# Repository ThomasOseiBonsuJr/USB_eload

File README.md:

# USB_eload
This is built off of my previous Electronic Load project, a now deleted repository. I wasn't happy with the state and the direction the project was heading so I am creating a new project.

# Features 
- Constant resistance, constant power, constant current, and constant voltage modes. 
- Software fan control instead of hardware fan control. (Hardware fan control was an interesting idea however I think implementing software fan control will allow for a 'clearer' path for project completion)
- 3D printed enclosure with venting for fan
- OLED display for fan speed, load current, voltage, resistance, power, and temperature

- 20V Max Voltage, 5A max current
- software (maybe hardware if it is more reliable) safety features to prevent overcurrent, overvoltage, and over temperature

- The e load will only be controlled with a usb connection 2.0 to a computer 
- Program that sends commands to change eload parameters (either a terminal program or a exe or something that involves an actual UI, currently leaning  towards a program with a UI due the coding experience that could be gained from that)

# Roadmap
- Rough sketch of enclosure UI
- Research electronic load arcitecture (I think the main reason why I consider the first attempt at this project a failure is because of the minimal amount of research and low expectations of the electronic load. While this project will not come near an off the shelf solution it should at least be suitable for an electronics beginner like me)
- Research constant power, constant resistance, and constant voltage modes
- Learn fusion 360 
- Research the usb 2.0 protocol
- Decide MCU (mcu on old electronic load might be good enough)
- Block diagrams of subsystems in the electronic load
- 1st draft of schematic and layout 
- Review, iterate if needed
- Design enclosure
- Order parts, solder, and test (currently away from home so this last step might be delayed for a bit)

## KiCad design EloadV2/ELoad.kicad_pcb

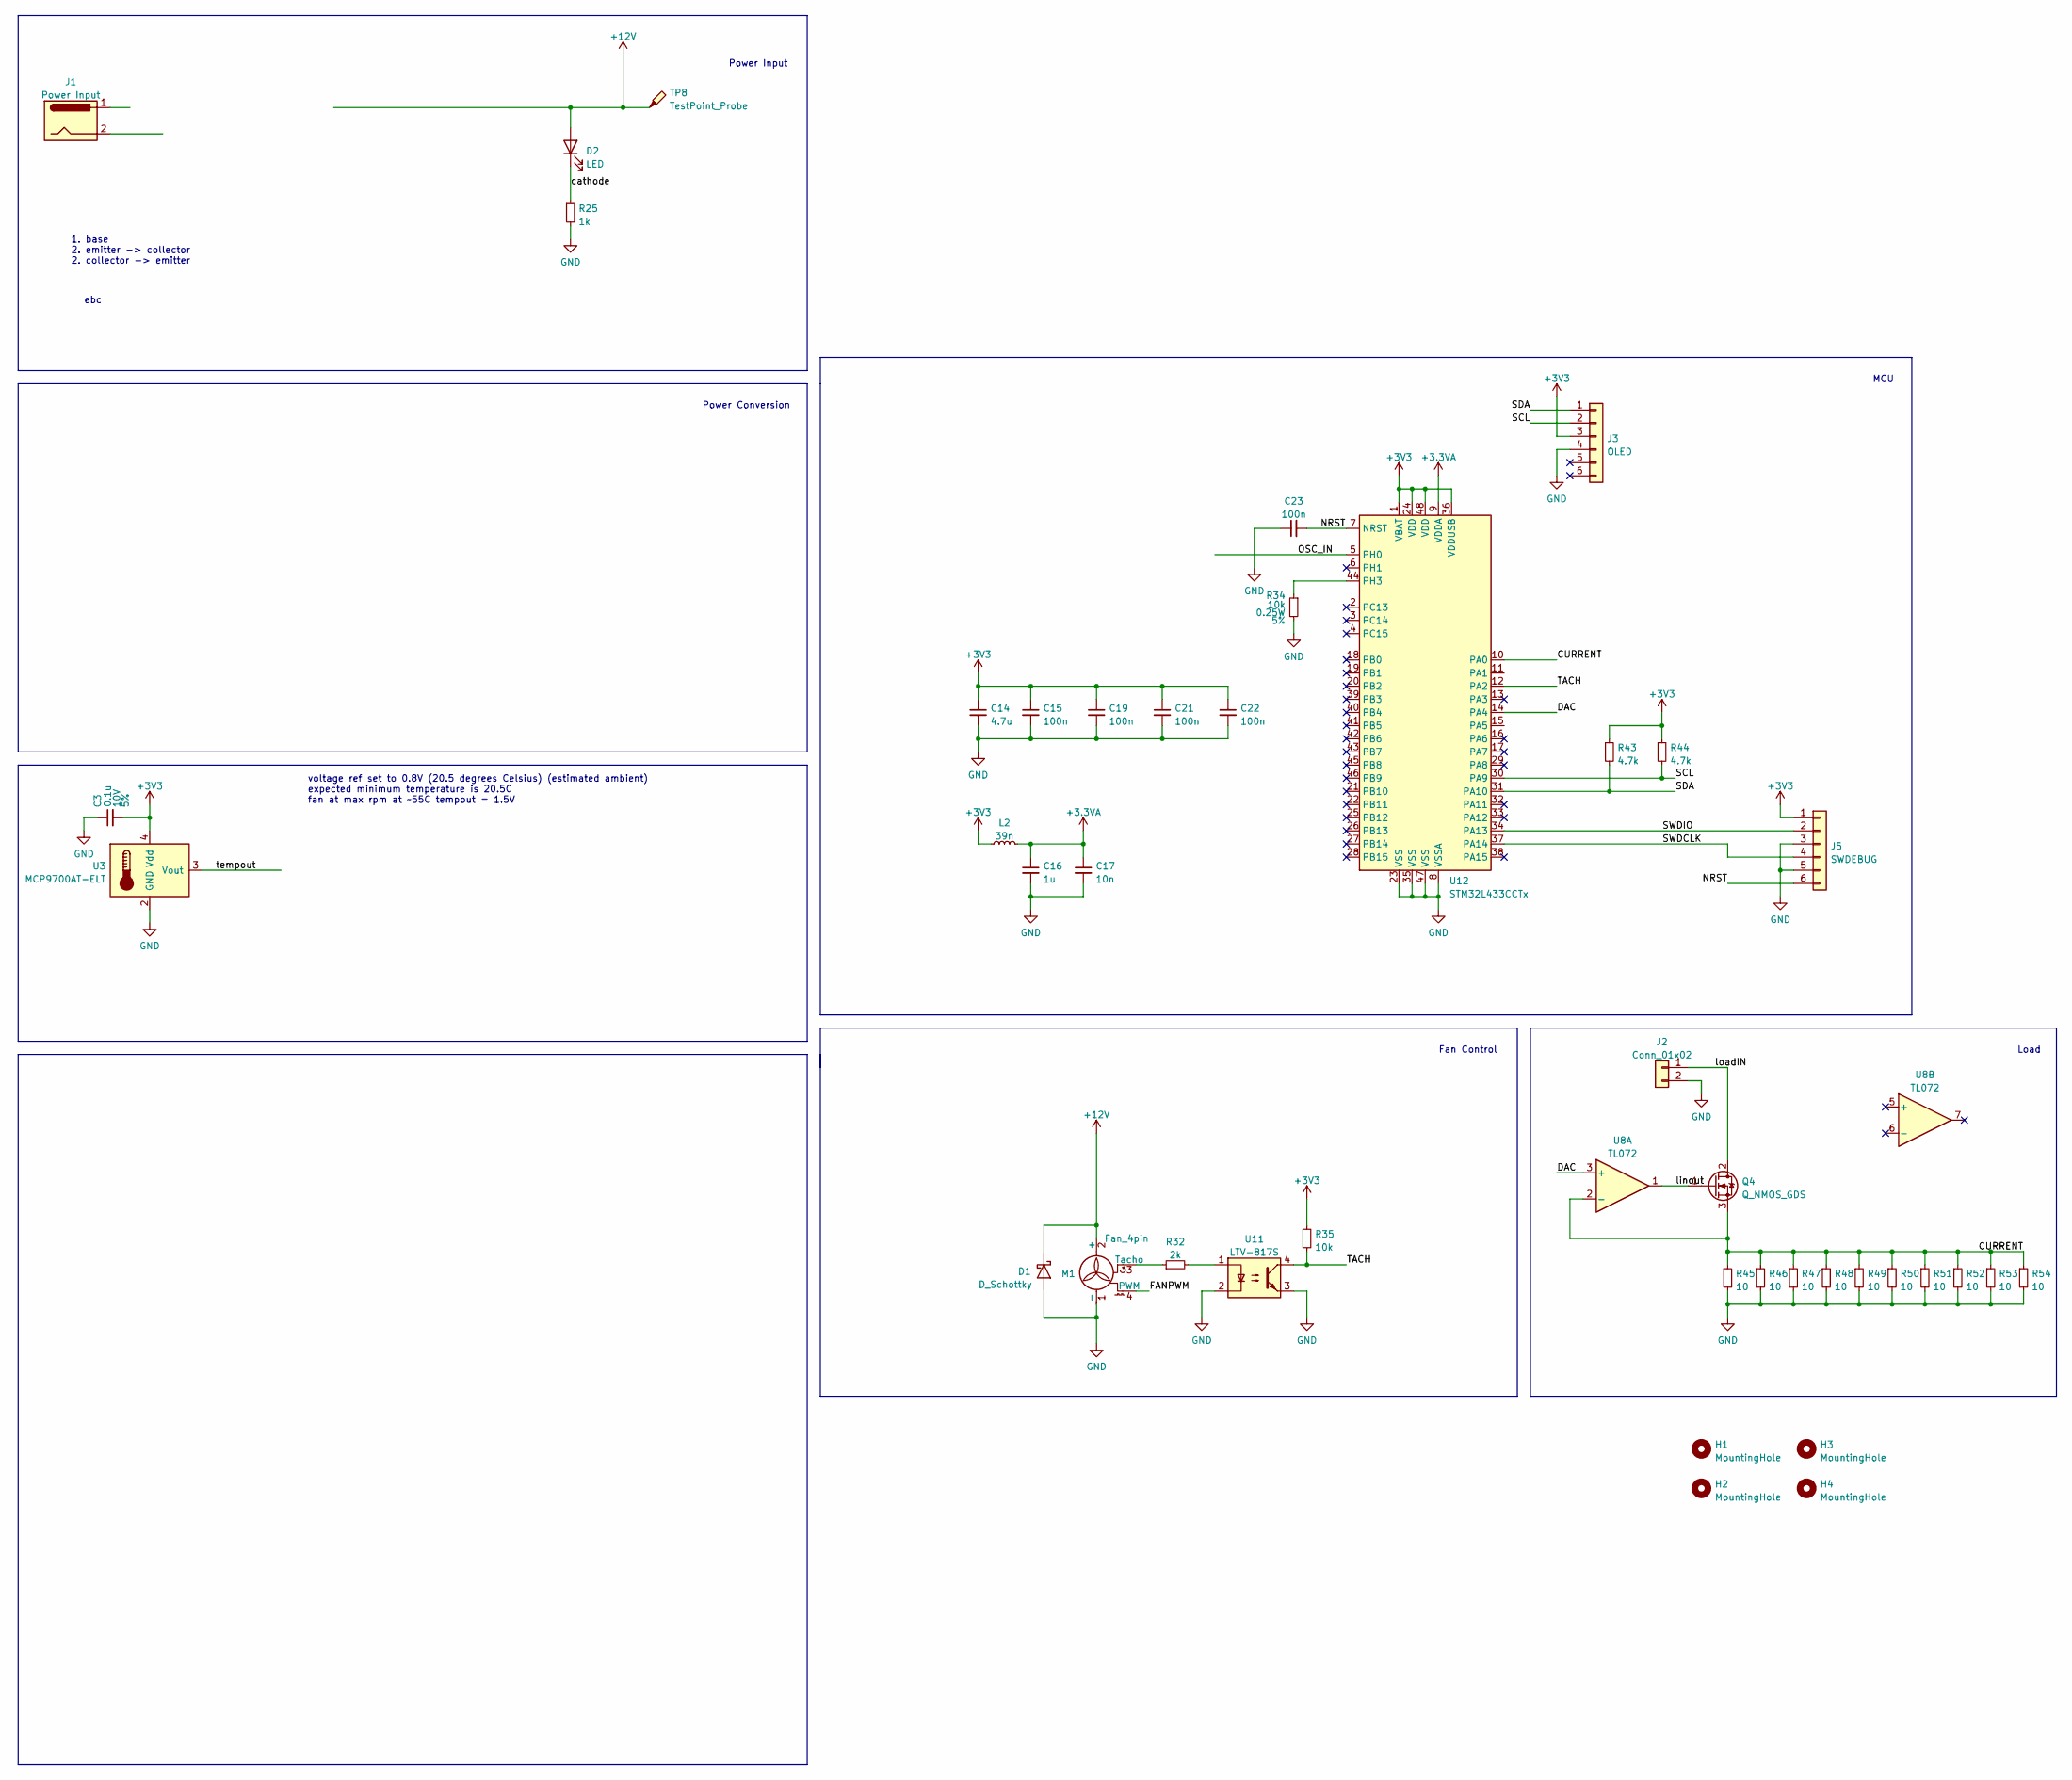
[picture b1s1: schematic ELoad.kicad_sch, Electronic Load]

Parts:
C3: 0.1u; C_0603_1608Metric_Pad1.08x0.95mm_HandSolder; Rating 10V; Tolerance 5%
C14: 4.7u; C_0603_1608Metric_Pad1.08x0.95mm_HandSolder
C15, C19, C21, C22, C23: 100n; C_0603_1608Metric_Pad1.08x0.95mm_HandSolder
C16: 1u; C_0603_1608Metric_Pad1.08x0.95mm_HandSolder
C17: 10n; C_0603_1608Metric_Pad1.08x0.95mm_HandSolder
D1: D_Schottky; D_SMA_Handsoldering
D2: LED; D_1210_3225Metric_Pad1.42x2.65mm_HandSolder
H1, H2, H3, H4: MountingHole; MountingHole_4.3mm_M4_DIN965_Pad_TopBottom
J1: Power Input; BarrelJack_CUI_PJ-063AH_Horizontal
J2: Conn_01x02; TerminalBlock_Phoenix_PT-1,5-2-3.5-H_1x02_P3.50mm_Horizontal
J3: OLED; PinSocket_1x06_P2.54mm_Vertical
J5: SWDEBUG; PinSocket_1x06_P2.54mm_Vertical
L2: 39n; L_1210_3225Metric
M1: Fan_4pin; FanPinHeader_1x04_P2.54mm_Vertical_NoRandomHole
Q4: Q_NMOS_GDS; TO-220-3_Horizontal_TabUp
R25: 1k; R_0805_2012Metric_Pad1.20x1.40mm_HandSolder
R32: 2k; R_0805_2012Metric_Pad1.20x1.40mm_HandSolder
R34: 10k; R_0805_2012Metric_Pad1.20x1.40mm_HandSolder; Rating 0.25W; Tolerance 5%
R35: 10k; R_0805_2012Metric_Pad1.20x1.40mm_HandSolder
R43, R44: 4.7k; R_0805_2012Metric_Pad1.20x1.40mm_HandSolder
R45, R46, R47, R48, R49, R50, R51, R52, R53, R54: 10; R_Axial_DIN0207_L6.3mm_D2.5mm_P10.16mm_Horizontal
TP8: TestPoint_Probe; TestPoint_Pad_1.5x1.5mm
U3: MCP9700AT-ELT; SOT-353_SC-70-5
U8: TL072; SOIC-8_3.9x4.9mm_P1.27mm
U11: LTV-817S; SMDIP-4_W9.53mm
U12: STM32L433CCTx; LQFP-48_7x7mm_P0.5mm

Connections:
+3.3VA: C16.1, C17.1, L2.2, U12.9 (VDDA)
+3V3: C14.1, C15.1, C19.1, C21.1, C22.1, J3.3, J5.1, L2.1, R35.1, R43.1, R44.1, U12.1 (VBAT), U12.24 (VDD), U12.36 (VDDUSB), U12.48 (VDD); also elsewhere on the board
+5V: C3.2, U3.4 (Vdd)
+12V: D1.1 (K), D2.2 (A), M1.2 (+), TP8.1
/CURRENT: Q4.3 (S), R45.1, R46.1, R47.1, R48.1, R49.1, R50.1, R51.1, R52.1, R53.1, R54.1, U8.2 (-), U12.10 (PA0)
/DAC: U8.3 (+), U12.14 (PA4)
/FANPWM: M1.4 (PWM)
/NRST: C23.2, J5.6, U12.7 (NRST)
/OSC_IN: U12.5 (PH0); also elsewhere on the board
/SCL: J3.2, R44.2, U12.30 (PA9)
/SDA: J3.1, R43.2, U12.31 (PA10)
/SWDCLK: J5.4, U12.37 (PA14)
/SWDIO: J5.2, U12.34 (PA13)
/TACH: R35.2, U11.4, U12.12 (PA2)
/cathode: D2.1 (K), R25.1
/linout: Q4.1 (G), U8.1
/loadIN: J2.1, Q4.2 (D)
/tempout: U3.3 (Vout)
GND: C3.1, C14.2, C15.2, C16.2, C17.2, C19.2, C21.2, C22.2, C23.1, D1.2 (A), J2.2, J3.4, J5.3, J5.5, M1.1 (-), R25.2, R34.2, R45.2, R46.2, R47.2, R48.2, R49.2, R50.2, R51.2, R52.2, R53.2, R54.2, U3.2 (GND), U11.2, U11.3, U12.8 (VSSA), U12.23 (VSS), U12.35 (VSS), U12.47 (VSS); also elsewhere on the board
unnamed: M1.3 (Tacho), R32.1
unnamed: R32.2, U11.1
unnamed: R34.1, U12.44 (PH3)

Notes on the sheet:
MCU
Power Input
1. base 2. emitter -> collector 2. collector -> emitter
Fan Control
ebc
Load
voltage ref set to 0.8V (20.5 degrees Celsius) (estimated ambient) expected minimum temperature is 20.5C fan at max rpm at ~55C tempout = 1.5V
Power Conversion

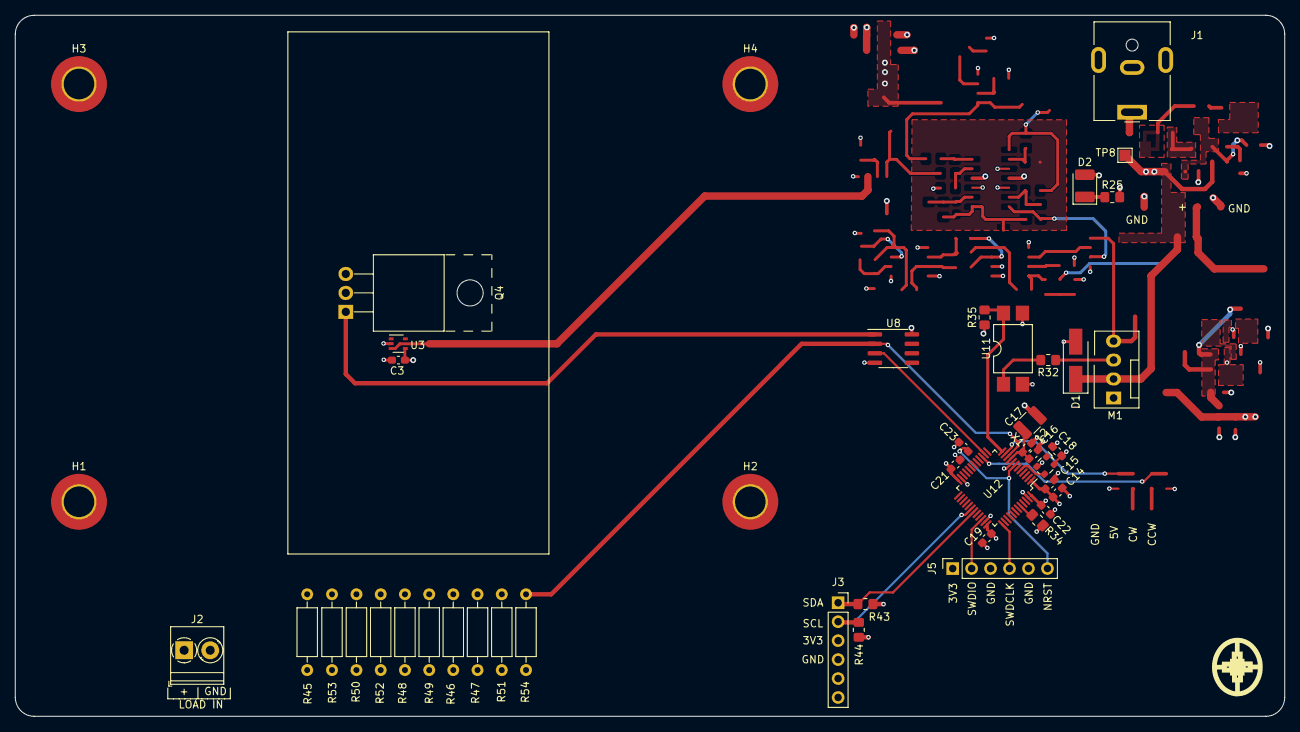
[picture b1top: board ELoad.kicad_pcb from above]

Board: 4 copper layers, 170.2 x 94.0 mm, 45 parts (0 on the bottom side), 20 nets.

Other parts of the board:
C18: 0.1u; C_0603_1608Metric_Pad1.08x0.95mm_HandSolder
X1: ECS-2520MV-160-CN-TR; Oscillator_SMD_ECS_2520MV-xxx-xx-4Pin_2.5x2.0mm

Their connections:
+3V3: C18.1, X1.4 (VDD); also elsewhere on the board
/OSC_IN: X1.3 (OUT); also elsewhere on the board
GND: C18.2, X1.2 (GND); also elsewhere on the board

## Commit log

2023-09-22 moving to new repo, changing scope of project, swapping to git bash instead of github desktop
2023-09-22 removing power, waveform generation, op amp pi, button latch
2023-09-23 finished readme and added planned ui
2023-12-14 Read me changes
